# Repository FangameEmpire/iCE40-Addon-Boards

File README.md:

# iCE40-Addon-Boards
A collection of add-on boards containing an iCE40 FPGA and the required supporting logic. Used to add FPGA functionality to existing hardware platforms, particularly microcontrollers. The boards are currently a work in progress. Currently, development prototypes are being tested, and the add-on boards will be designed once testing is complete.

## Planned platforms for add-on boards
-Arduino Uno

-Raspberry Pi Pico

-Seeed XIAO

-Adafruit Feather?

-QWIIC-only breakout?

## Testing hardware

## Addon board mockups
Work-in-progress screenshots of boards still being designed.

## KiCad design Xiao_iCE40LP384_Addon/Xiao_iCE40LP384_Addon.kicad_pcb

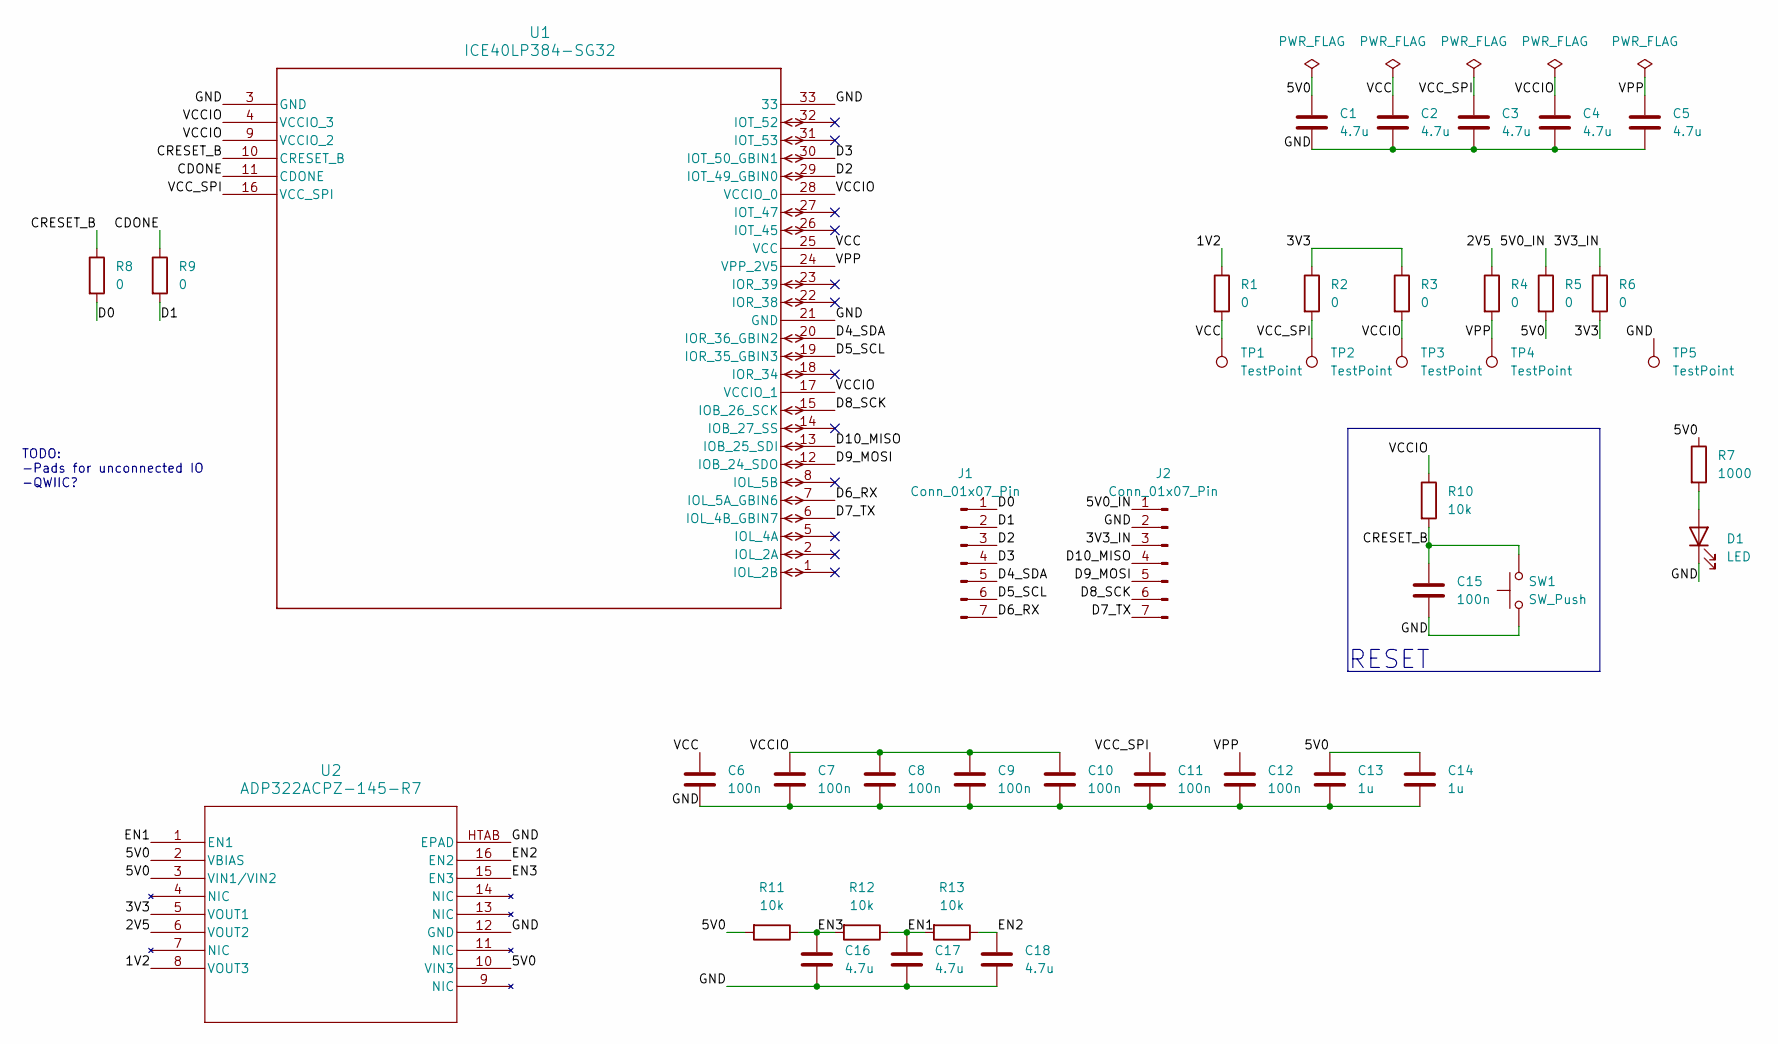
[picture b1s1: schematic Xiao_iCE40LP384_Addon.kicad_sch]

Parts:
C1, C2, C3, C4, C5, C16, C17, C18: 4.7u; C_0402_1005Metric
C6, C7, C8, C9, C10, C11, C12, C15: 100n; C_0402_1005Metric
C13, C14: 1u; C_0402_1005Metric
D1: LED; LED_0603_1608Metric
J1, J2: Conn_01x07_Pin; PinSocket_1x07_P2.54mm_Vertical
R1, R2, R3, R4, R5, R6, R8, R9: 0; R_0402_1005Metric
R7: 1000; R_0402_1005Metric
R10, R11, R12, R13: 10k; R_0402_1005Metric
SW1: SW_Push; Panasonic_EVQPUJ_EVQPUA
TP1, TP2, TP3, TP4, TP5: TestPoint; TestPoint_Pad_1.0x1.0mm
U1: ICE40LP384-SG32; QFNS32_LAT
U2: ADP322ACPZ-145-R7; CP_16_22_ADI

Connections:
/1V2: R1.1, U2.8 (VOUT3)
/2V5: R4.1, U2.6 (VOUT2)
/3V3: R2.1, R3.1, R6.2, U2.5 (VOUT1)
/3V3_IN: J2.3, R6.1
/5V0: C1.1, C13.1, C14.1, R5.2, R7.1, R11.2, U2.2 (VBIAS), U2.3 (VIN1/VIN2), U2.10 (VIN3)
/5V0_IN: J2.1, R5.1
/CDONE: R9.1, U1.11 (CDONE)
/CRESET_B: C15.1, R8.1, R10.2, SW1.2, U1.10 (CRESET_B)
/D0: J1.1, R8.2
/D1: J1.2, R9.2
/D2: J1.3, U1.29 (IOT_49_GBIN0)
/D3: J1.4, U1.30 (IOT_50_GBIN1)
/D4_SDA: J1.5, U1.20 (IOR_36_GBIN2)
/D5_SCL: J1.6, U1.19 (IOR_35_GBIN3)
/D6_RX: J1.7, U1.7 (IOL_5A_GBIN6)
/D7_TX: J2.7, U1.6 (IOL_4B_GBIN7)
/D8_SCK: J2.6, U1.15 (IOB_26_SCK)
/D9_MOSI: J2.5, U1.12 (IOB_24_SDO)
/D10_MISO: J2.4, U1.13 (IOB_25_SDI)
/EN1: C17.1, R12.1, R13.2, U2.1 (EN1)
/EN2: C18.1, R13.1, U2.16 (EN2)
/EN3: C16.1, R11.1, R12.2, U2.15 (EN3)
/GND: C1.2, C2.2, C3.2, C4.2, C5.2, C6.2, C7.2, C8.2, C9.2, C10.2, C11.2, C12.2, C13.2, C14.2, C15.2, C16.2, C17.2, C18.2, D1.1 (K), J2.2, SW1.1, TP5.1, U1.3 (GND), U1.21 (GND), U1.33, U2.12 (GND), U2.HTAB (EPAD)
/VCC: C2.1, C6.1, R1.2, TP1.1, U1.25 (VCC)
/VCCIO: C4.1, C7.1, C8.1, C9.1, C10.1, R3.2, R10.1, TP3.1, U1.4 (VCCIO_3), U1.9 (VCCIO_2), U1.17 (VCCIO_1), U1.28 (VCCIO_0)
/VCC_SPI: C3.1, C11.1, R2.2, TP2.1, U1.16 (VCC_SPI)
/VPP: C5.1, C12.1, R4.2, TP4.1, U1.24 (VPP_2V5)
unnamed: D1.2 (A), R7.2

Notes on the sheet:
RESET
TODO: -Pads for unconnected IO -QWIIC?

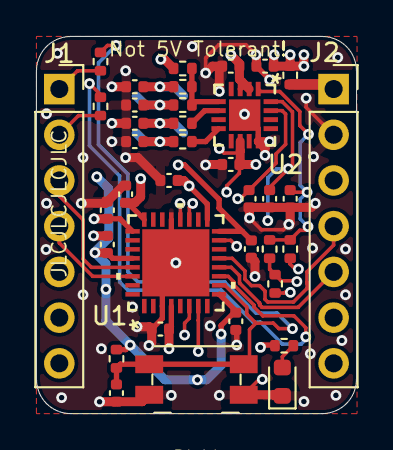
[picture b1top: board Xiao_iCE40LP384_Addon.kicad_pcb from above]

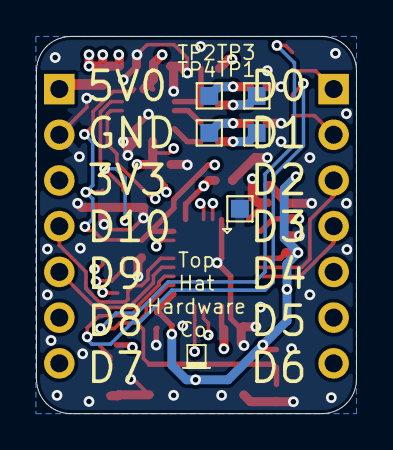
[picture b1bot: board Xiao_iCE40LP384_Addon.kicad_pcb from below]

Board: 4 copper layers, 17.8 x 21.0 mm, 42 parts (5 on the bottom side), 28 nets.

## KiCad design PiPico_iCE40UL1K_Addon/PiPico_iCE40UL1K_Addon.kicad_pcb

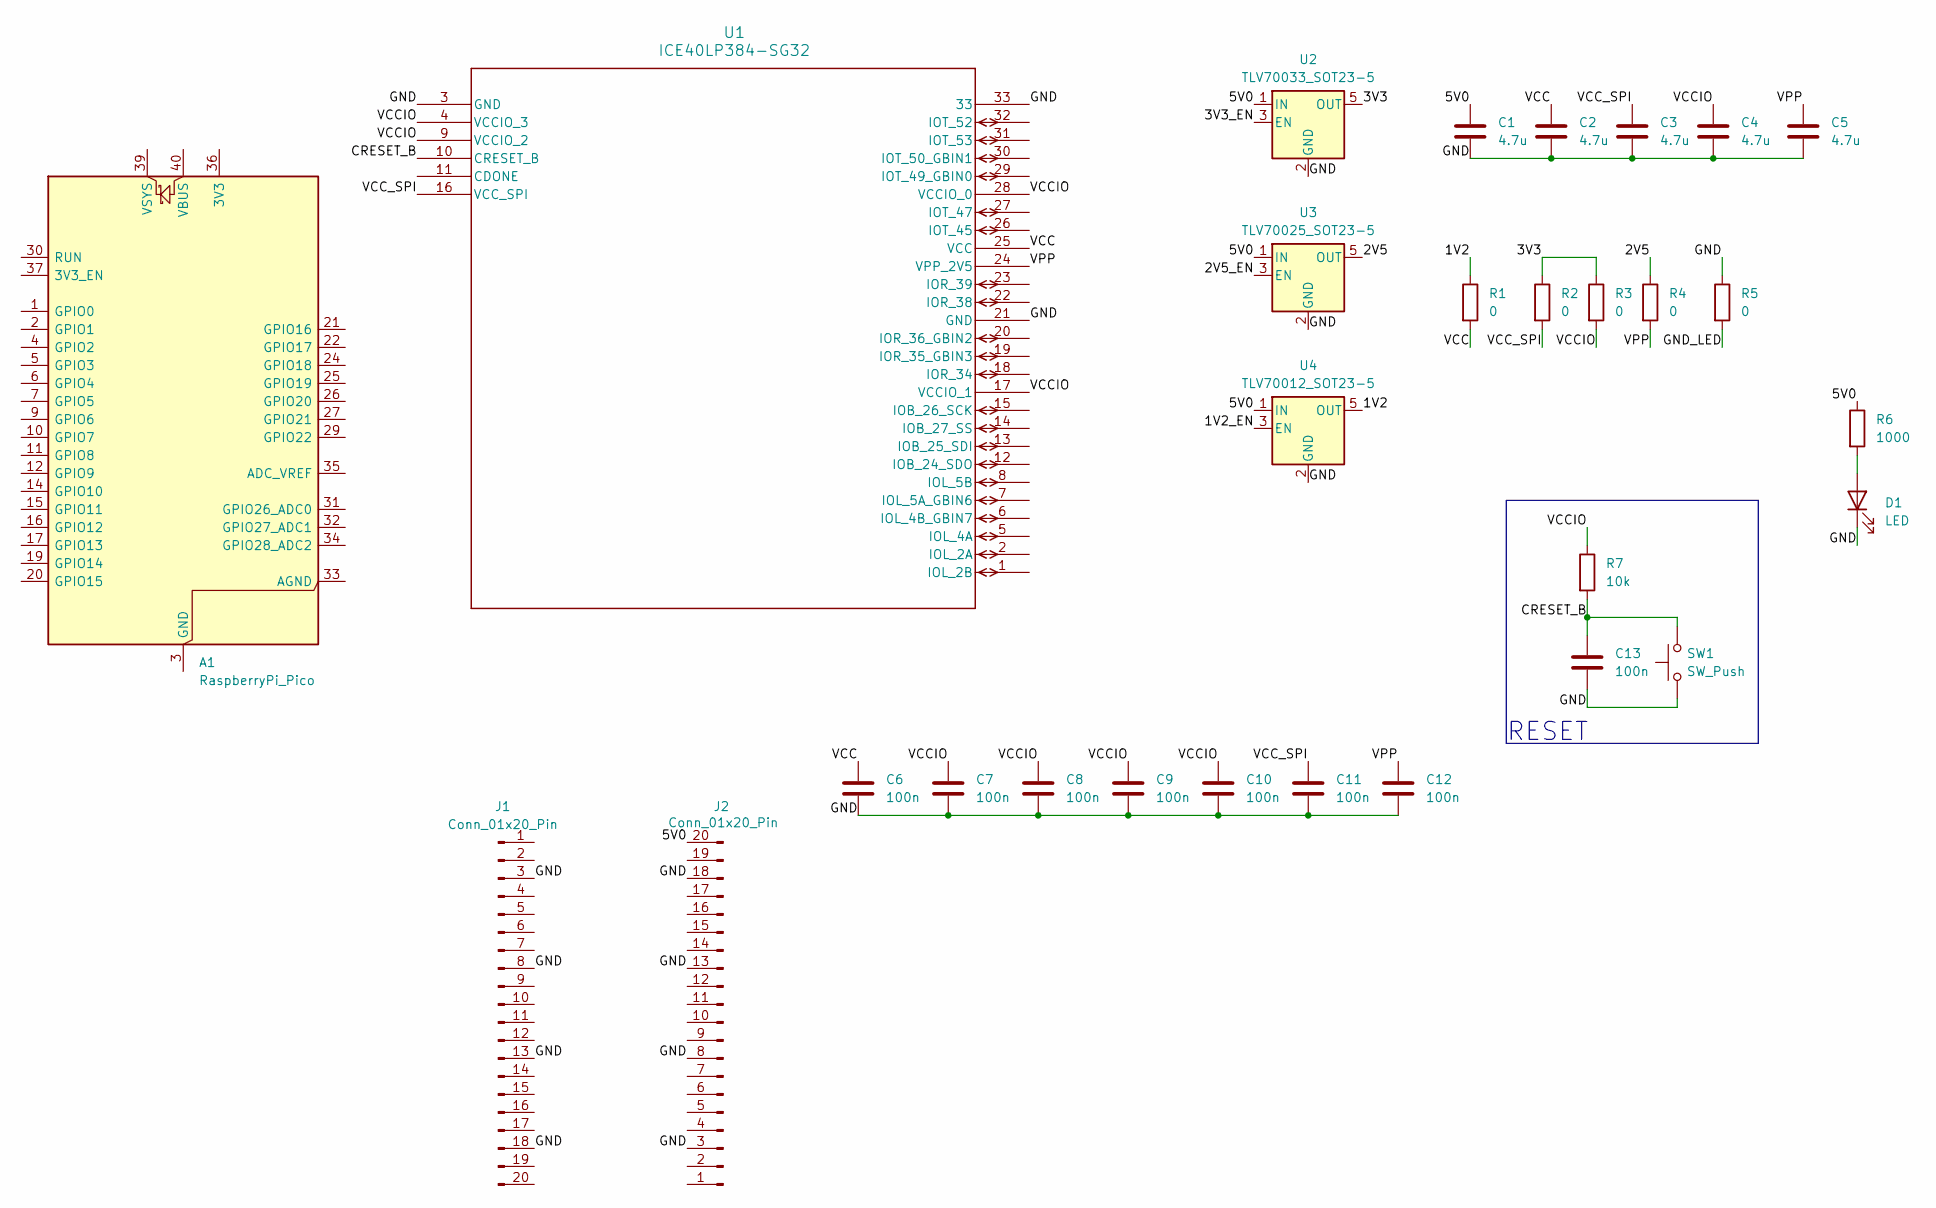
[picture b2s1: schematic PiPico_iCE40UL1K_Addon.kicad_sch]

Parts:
A1: RaspberryPi_Pico; RaspberryPi_Pico_Common_Unspecified
C1, C2, C3, C4, C5: 4.7u; C_0603_1608Metric
C6, C7, C8, C9, C10, C11, C12, C13: 100n; C_0603_1608Metric
D1: LED; LED_0603_1608Metric
J1, J2: Conn_01x20_Pin; PinHeader_1x20_P2.54mm_Vertical
R1, R2, R3, R4, R5: 0; R_0603_1608Metric
R6: 1000; R_0603_1608Metric
R7: 10k; R_0603_1608Metric
SW1: SW_Push; Panasonic_EVQPUJ_EVQPUA
U1: ICE40LP384-SG32; QFNS32_LAT
U2: TLV70033_SOT23-5; SOT-23-5
U3: TLV70025_SOT23-5; SOT-23-5
U4: TLV70012_SOT23-5; SOT-23-5

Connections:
/1V2: R1.1, U4.5 (OUT)
/1V2_EN: U4.3 (EN)
/2V5: R4.1, U3.5 (OUT)
/2V5_EN: U3.3 (EN)
/3V3: R2.1, R3.1, U2.5 (OUT)
/3V3_EN: U2.3 (EN)
/5V0: C1.1, J2.20, R6.1, U2.1 (IN), U3.1 (IN), U4.1 (IN)
/CRESET_B: C13.1, R7.2, SW1.2, U1.10 (CRESET_B)
/GND: C1.2, C2.2, C3.2, C4.2, C5.2, C6.2, C7.2, C8.2, C9.2, C10.2, C11.2, C12.2, C13.2, D1.1 (K), J1.3, J1.8, J1.13, J1.18, J2.3, J2.8, J2.13, J2.18, R5.1, SW1.1, U1.3 (GND), U1.21 (GND), U1.33, U2.2 (GND), U3.2 (GND), U4.2 (GND)
/GND_LED: R5.2
/VCC: C2.1, C6.1, R1.2, U1.25 (VCC)
/VCCIO: C4.1, C7.1, C8.1, C9.1, C10.1, R3.2, R7.1, U1.4 (VCCIO_3), U1.9 (VCCIO_2), U1.17 (VCCIO_1), U1.28 (VCCIO_0)
/VCC_SPI: C3.1, C11.1, R2.2, U1.16 (VCC_SPI)
/VPP: C5.1, C12.1, R4.2, U1.24 (VPP_2V5)
unnamed: A1.3 (GND), A1.8 (GND), A1.13 (GND), A1.18 (GND), A1.23 (GND), A1.28 (GND), A1.38 (GND)
unnamed: D1.2 (A), R6.2

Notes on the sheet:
RESET

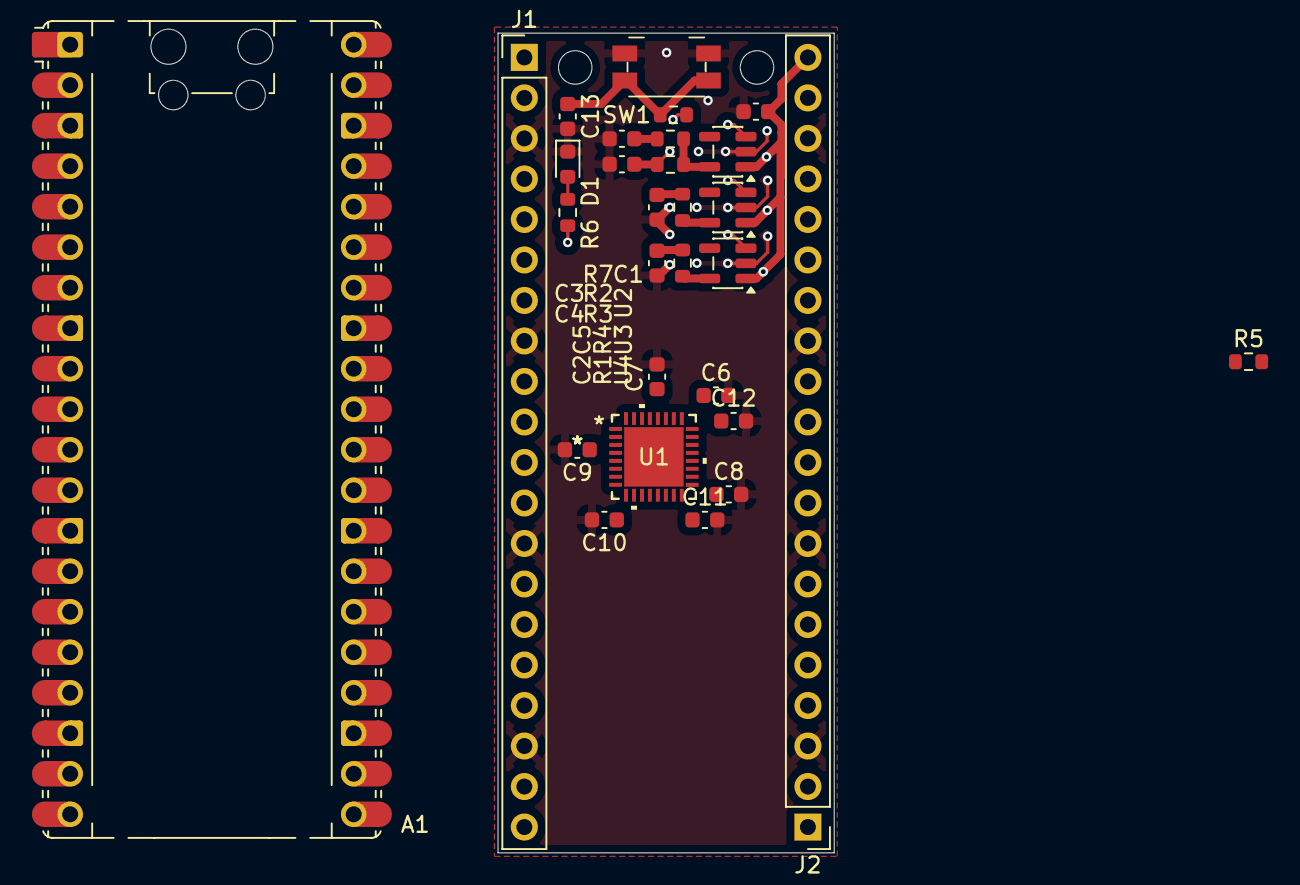
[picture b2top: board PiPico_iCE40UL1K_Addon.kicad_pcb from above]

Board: 4 copper layers, 21.1 x 51.4 mm, 29 parts (0 on the bottom side), 12 nets.

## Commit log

2026-03-16 Started Pi Pico floorplanning
2026-03-16 Add planned boards to readme
2026-03-16 Add images
2026-03-23 Finished power supply placement and some routing. FPGA power from power supply not routed.
2026-03-23 Add mockups sectino to readme
2026-03-23 Add mockups section to readme
2026-03-23 Update Pi Pico floorplan image with power supply layout
2026-03-23 Change file extension caps
2026-03-31 Started XIAO breakout, did some basic floorplanning
2026-04-01 Finished most of the XIAO floorplan, need to route FPGA caps
2026-04-03 XIAO done, as long as no problems come up during prototype testing
2026-04-03 Noted lack of 5V tolerance
2026-04-08 Improve silkscreen, fix ADP322 footprint error
2026-04-09 Slow down RC timer and add test points to power supply
2026-04-09 Slight improvements to ground
2026-04-09 Gerbers.zip for manufacturing
